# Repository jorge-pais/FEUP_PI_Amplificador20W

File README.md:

# FEUP PI Amplificador20W
 
20W Audio Amplifier circuit developed for the capstone project of the Bachelor in Electrical and Computer Enginnering course.
The power amplifier features 2 voltage gain stages and a Class AB output stage, along with a DC servo for low output DC offset, a power supply filter featuring a capacitance multiplier and an optional input network.

### PCB Front 3D view

### PCB Rear 3D view

## Credits to:
David Rainho\
Gustavo Santos\
Inês Brandão\
Jorge Ribeiro\
Margarida Leal\
Rodrigo Santacomba\
Tiago Ribeiro

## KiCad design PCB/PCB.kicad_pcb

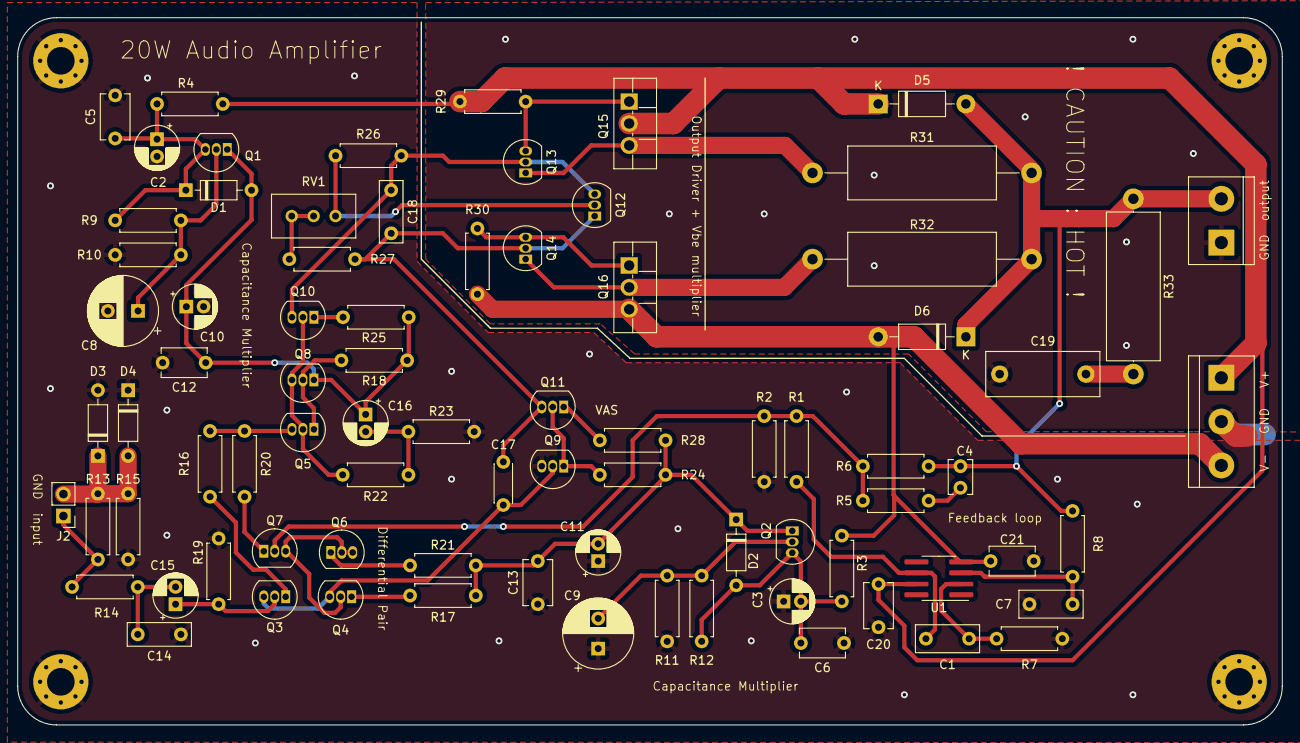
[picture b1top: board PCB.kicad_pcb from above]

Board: 2 copper layers, 146.6 x 82.0 mm, 85 parts (0 on the bottom side), 41 nets.

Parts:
C1, C7: 470n; C_Rect_L7.2mm_W3.0mm_P5.00mm_FKS2_FKP2_MKS2_MKP2
C2, C3: 100u; CP_Radial_D5.0mm_P2.00mm
C4: 2p2; C_Disc_D3.8mm_W2.6mm_P2.50mm
C5, C6, C12, C13, C20, C21: 100n; C_Disc_D5.1mm_W3.2mm_P5.00mm
C8, C9: 100u; CP_Radial_D8.0mm_P3.50mm
C10, C11, C15, C16: 10u; CP_Radial_D5.0mm_P2.00mm
C14: 3n3; C_Rect_L7.2mm_W2.5mm_P5.00mm_FKS2_FKP2_MKS2_MKP2
C17: 47p; C_Disc_D4.3mm_W1.9mm_P5.00mm
C18: 220n; C_Rect_L7.0mm_W2.5mm_P5.00mm
C19: 100n; C_Rect_L13.0mm_W5.0mm_P10.00mm_FKS3_FKP3_MKS4
D1, D2: 1N914; D_DO-35_SOD27_P7.62mm_Horizontal
D3, D4: 1N4148; D_DO-35_SOD27_P7.62mm_Horizontal
D5, D6: 1N4004; D_DO-41_SOD81_P10.16mm_Horizontal
H1, H2, H3, H4: MountingHole_Pad; MountingHole_3.2mm_M3_Pad_Via
J1: Screw_Terminal_01x03; TerminalBlock_bornier-3_P5.08mm
J2: Conn_01x02; PinHeader_1x02_P2.54mm_Vertical
J3: Screw_Terminal_01x02; TerminalBlock_bornier-2_P5.08mm
Q1: 2N3904; TO-92_Inline
Q2: 2N3906; TO-92_Inline
Q3, Q5, Q7, Q8, Q10: 2N4403; TO-92_Inline
Q4, Q6, Q9, Q11, Q12: 2N4401; TO-92_Inline
Q13: 2N5550; TO-92_Inline
Q14: 2N5401; TO-92_Inline
Q15: MJF15031; TO-220F-3_Vertical
Q16: MJF15030; TO-220F-3_Vertical
R1, R7, R8: 330k; R_Axial_DIN0207_L6.3mm_D2.5mm_P7.62mm_Horizontal
R2: 1k; R_Axial_DIN0207_L6.3mm_D2.5mm_P7.62mm_Horizontal
R3, R4: 10; R_Axial_DIN0207_L6.3mm_D2.5mm_P7.62mm_Horizontal
R5, R18: 100; R_Axial_DIN0207_L6.3mm_D2.5mm_P7.62mm_Horizontal
R6, R19: 8k2; R_Axial_DIN0207_L6.3mm_D2.5mm_P7.62mm_Horizontal
R9, R12: 220; R_Axial_DIN0207_L6.3mm_D2.5mm_P7.62mm_Horizontal
R10, R11: 22k; R_Axial_DIN0207_L6.3mm_D2.5mm_P7.62mm_Horizontal
R13: 100k; R_Axial_DIN0207_L6.3mm_D2.5mm_P7.62mm_Horizontal
R14: 50; R_Axial_DIN0207_L6.3mm_D2.5mm_P7.62mm_Horizontal
R15: 4.7; R_Axial_DIN0207_L6.3mm_D2.5mm_P7.62mm_Horizontal
R16, R20, R29, R30: 330; R_Axial_DIN0207_L6.3mm_D2.5mm_P7.62mm_Horizontal
R17, R21: 180; R_Axial_DIN0207_L6.3mm_D2.5mm_P7.62mm_Horizontal
R22, R23: 15k; R_Axial_DIN0207_L6.3mm_D2.5mm_P7.62mm_Horizontal
R24, R26: 820; R_Axial_DIN0207_L6.3mm_D2.5mm_P7.62mm_Horizontal
R25: 68; R_Axial_DIN0207_L6.3mm_D2.5mm_P7.62mm_Horizontal
R27: 390; R_Axial_DIN0207_L6.3mm_D2.5mm_P7.62mm_Horizontal
R28: 33; R_Axial_DIN0207_L6.3mm_D2.5mm_P7.62mm_Horizontal
R31, R32: 0.22; R_Axial_DIN0617_L17.0mm_D6.0mm_P25.40mm_Horizontal
R33: 5; R_Axial_DIN0617_L17.0mm_D6.0mm_P20.32mm_Horizontal
RV1: 1k; Potentiometer_Bourns_3296W_Vertical
U1: OPA1641; SOIC-8_3.9x4.9mm_P1.27mm

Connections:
/Input: J2.1, R13.1, R14.1
/Output: C4.2, D5.2 (A), D6.1 (K), J3.2, R6.2, R8.1, R31.2, R32.1, R33.1
/Vcc_reg: C10.1, C12.1, C16.1, D1.2 (A), Q1.1 (E), Q8.1 (E), R18.1, R25.1
/Vee_reg: C11.2, C13.2, D2.1 (K), Q2.1 (E), R17.2, R21.2, R24.2, R28.2
/Vinput+: C15.1, Q3.2 (B), R19.1
/Vinput-: Q7.2 (B), R1.1, R2.1, R5.1, R6.1
/filter_res: C16.2, R22.2, R23.1
/op_in+: C7.1, R8.2, U1.3 (+)
/op_in-: C1.2, R7.1, U1.2 (-)
/op_out: C1.1, R1.2, U1.6
/pair_tail: Q5.3 (C), R16.1, R20.1
/vb1: C8.1, Q1.2 (B), R9.2, R10.1
/vb2: C9.2, Q2.2 (B), R11.2, R12.1
/vb5: Q5.2 (B), Q8.3 (C), Q10.2 (B), R22.1
/vb12: Q12.2 (B), R26.2, RV1.1
/vb15: Q13.3 (C), Q15.1 (B), R29.2
/vb16: Q14.3 (C), Q16.1 (B), R30.1
/vc1: C2.1, C5.1, D1.1 (K), Q1.3 (C), R4.2, R9.1
/vc2: C3.2, C6.2, D2.2 (A), Q2.3 (C), R3.2, R12.2
/vc3: C17.1, Q3.3 (C), Q4.3 (C), Q9.2 (B)
/vc7: Q4.2 (B), Q6.2 (B), Q6.3 (C), Q7.3 (C)
/vc12: C18.1, Q10.3 (C), Q12.3 (C), Q13.2 (B), R26.1
/vc15: Q13.1 (E), Q15.3 (E), R31.1
/vc16: Q14.1 (E), Q16.2 (C), R32.2
/ve3: Q3.1 (E), R16.2
/ve4: Q4.1 (E), R17.1
/ve5: Q5.1 (E), Q8.2 (B), R18.2
/ve6: Q6.1 (E), R21.1
/ve7: Q7.1 (E), R20.2
/ve9: Q9.1 (E), Q11.2 (B), R24.1
/ve10: Q10.1 (E), R25.2
/ve11: Q11.1 (E), R28.1
/ve12: C17.2, C18.2, Q11.3 (C), Q12.1 (E), Q14.2 (B), R27.2
GND: C2.2, C3.1, C5.2, C6.1, C7.2, C8.2, C9.1, C10.2, C11.1, C12.2, C13.1, C14.2, C19.2, C20.2, C21.1, D3.2 (A), D4.1 (K), H1.1, H2.1, H3.1, H4.1, J1.2, J3.1, Q9.3 (C), R2.2, R7.2, R10.2, R11.1, R15.2, R19.2, R23.2
GND2: D3.1 (K), D4.2 (A), J2.2, R13.2, R15.1
unnamed: C4.1, R5.2
unnamed: C14.1, C15.2, R14.2
unnamed: C19.1, R33.2
unnamed: R27.1, RV1.2, RV1.3
VCC: C20.1, D5.1 (K), J1.1, Q15.2 (C), R4.1, R29.1, U1.7 (V+)
VEE: C21.2, D6.2 (A), J1.3, Q16.3 (E), R3.1, R30.2, U1.4 (V-)
